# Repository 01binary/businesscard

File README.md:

# Interactive Business Card

A two-sided PCB business card designed in `KiCad 9`, built around an `ESP32-S2-MINI-2` module, powered by `USB-C` or a `CR2032` coin cell.

+ Capacitive-Touch Piano Keys (`C4`–`C5`, one octave)
+ Piezo Speaker (Monophonic Tone Playback)
+ Capacitive Logo Touch Pad (Wake / Power Control)
+ USB-C or `CR2032` Power, Auto-Switched
+ Deep Sleep for Low Power Consumption

## Modules

The following module is placed onto the board:

|Module|Function|
|-|-|
|`ESP32-S2-MINI-2-N4`|MCU module with native USB, capacitive-touch inputs, and deep sleep|

## Power

Power comes from either a `USB-C` connector (through a `3.3V` LDO regulator) or a `CR2032` coin cell battery.

A `TPS2121` power multiplexer (`U_PWR`) automatically prioritizes `USB` power when plugged in, and switches back to coin cell power when unplugged, with no interruption to the `3.3V` rail.

| Stage | Component | Function |
|-|-|-|
| `USB` → `3.3V` | `AP2112K-3.3` (`U2`) | LDO regulator, converts `VBUS` (`5V`) down to `3.3V` |
| `USB` / Battery Switch | `TPS2121` (`U_PWR`) | Selects `USB 3.3V` or `CR2032 3V`, prioritizing `USB` |
| Coin Cell | Keystone `3034` (`BT1`) | Holder for `20mm CR2032` battery |

Decoupling/bulk capacitors on the `3.3V` rail:

|Capacitor|Value|Purpose|
|-|-|-|
|`C1`|`100µF`|Bulk capacitor, stabilizes rail against low-frequency dips (battery power draw)|
|`C2`|`10µF`|LDO output filter|
|`C3`|`0.1µF`|Local high-frequency bypass near the MCU|

### USB-C Configuration

The `USB-C` receptacle (`J1`) is configured for `UFP` (Upstream Facing Port) mode, meaning the card acts as a `USB` device, not a host.

+ `CC1` and `CC2` are each pulled to `GND` through `5.1kΩ` resistors (`R1`, `R2`), advertising the device role per the `USB Type-C` spec.
+ Only one of `CC1`/`CC2` is active depending on cable orientation, but both are populated so the connector works either way.
+ When plugged in, the host detects the pull-downs and supplies `5V` on `VBUS`.
+ No `USB-PD` negotiation is needed since the board only draws default `5V` at low current.

## Touch Interface

The front of the card has 13 capacitive touch pads forming one octave of piano-style keys (`C4`–`C5`), plus a two-piece logo pad that is electrically bridged into a single touch input.

+ Touching a piano key plays its corresponding tone through the piezo speaker.
+ Touching the logo pad wakes the device from deep sleep and acts as the soft power button.
+ After a period of inactivity, the firmware drops to a reduced CPU frequency and then enters deep sleep; touching the logo is the wake source.
+ All touch pads and I/O are additionally brought out as test points for flexibility in layout and debugging.

## Audio

When a key is touched, the firmware plays a monophonic tone through a piezo transducer (`LS1`), driven differentially from two `GPIO` pins through `100Ω` series resistors (`R3`, `R4`).

## Buttons

|Button|Function|
|-|-|
|`SW1`|`RESET` — pulls `EN` low to reset the MCU|
|`SW2`|`BOOT` — pulls `GPIO0` low to enter flashing mode|

## Pins

|Pin|Function|
|-|-|
|`GPIO19`|USB `D-` (`J1`)|
|`GPIO20`|USB `D+` (`J1`)|
|`GPIO0`|`BOOT` Button (`SW2`)|
|`EN`|`RESET` Button (`SW1`)|
|`3V3`|Power input from `U_PWR` (`TPS2121`) `OUT`|
|`GPIO26`|Piezo Driver `A` → `R3` → `LS1 +`|
|`GPIO17`|Piezo Driver `B` → `R4` → `LS1 -`|
|`GPIO1`|Touch Key `C` (`TP1`)|
|`GPIO2`|Touch Key `C#` (`TP2`)|
|`GPIO3`|Touch Key `D` (`TP3`)|
|`GPIO4`|Touch Key `D#` (`TP4`)|
|`GPIO5`|Touch Key `E` (`TP5`)|
|`GPIO6`|Touch Key `F` (`TP6`)|
|`GPIO7`|Touch Key `F#` (`TP7`)|
|`GPIO8`|Touch Key `G` (`TP8`)|
|`GPIO9`|Touch Key `G#` (`TP9`)|
|`GPIO10`|Touch Key `A` (`TP10`)|
|`GPIO11`|Touch Key `A#` (`TP11`)|
|`GPIO12`|Touch Key `B` (`TP12`)|
|`GPIO13`|Touch Key `C` (octave up) (`TP13`)|
|`GPIO14`|Touch Logo Pad, wake source (`TP14`, bridged)|

## Bill of Materials

|Component|Description|
|-|-|
|[ESP32-S2-MINI-2-N4](https://www.digikey.com/en/products/result?keywords=ESP32-S2-MINI-2-N4)|Main MCU with native USB and capacitive-touch capability|
|[AP2112K-3.3TRG1DICT-ND](https://www.digikey.com/en/products/result?keywords=AP2112K-3.3TRG1)|`3.3V` LDO regulator for USB power source|
|[TPS2121RUXR](https://www.digikey.com/en/products/result?keywords=TPS2121RUXR)|Power multiplexer, auto-switches between USB `3.3V` and `CR2032` battery|
|[Keystone 3034](https://www.digikey.com/en/products/result?keywords=3034)|Holder for `20mm CR2032` battery|
|[UJ20-C-H-G-MSMT-5-P16-TR](https://www.digikey.com/en/products/result?keywords=UJ20-C-H-G-MSMT-5-P16-TR)|USB-C receptacle for power and programming|
|[TLSMDT3C020GLFS](https://www.digikey.com/en/products/detail/c-k/TLSMDT3C020GLFS/14553425)|`SW1`/`SW2` Momentary pushbutton, RESET (`EN`) and BOOT (`GPIO0`)|
|[SMT-1141-T-5-R](https://www.digikey.com/en/products/detail/pui-audio-inc/SMT-1141-T-5-R/6192576)|Piezo transducer, audio output for tone playback|
|[RMCF0603FT5K10CTND](https://www.digikey.com/en/products/result?keywords=RMCF0603FT5K10)|`5.1kΩ` `0603` resistor, USB-C `CC` pull-downs (`R1`, `R2`)|
|[RMCF0603JT100RCTND](https://www.digikey.com/en/products/result?keywords=RMCF0603JT100R)|`100Ω` `0603` resistor, piezo driver series protection (`R3`, `R4`)|
|[CL32A107MPVNNNE](https://www.digikey.com/en/products/result?keywords=CL32A107MPVNNNE)|`100µF` capacitor, bulk power stabilization (`C1`)|
|[GRM21BR61C106KE15K](https://www.digikey.com/en/products/result?keywords=GRM21BR61C106KE15K)|`10µF` `0805` capacitor, LDO output filter (`C2`)|
|[CS0805KKX7R0BB104](https://www.digikey.com/en/products/result?keywords=CS0805KKX7R0BB104)|`0.1µF` `0603` capacitor, local bypass near MCU (`C3`)|

`TP1`–`TP13` are capacitive piano key electrodes (`C4`–`C5`); `TP14` is the two-piece logo pad bridged into a single wake-source input. Neither requires a physical component.

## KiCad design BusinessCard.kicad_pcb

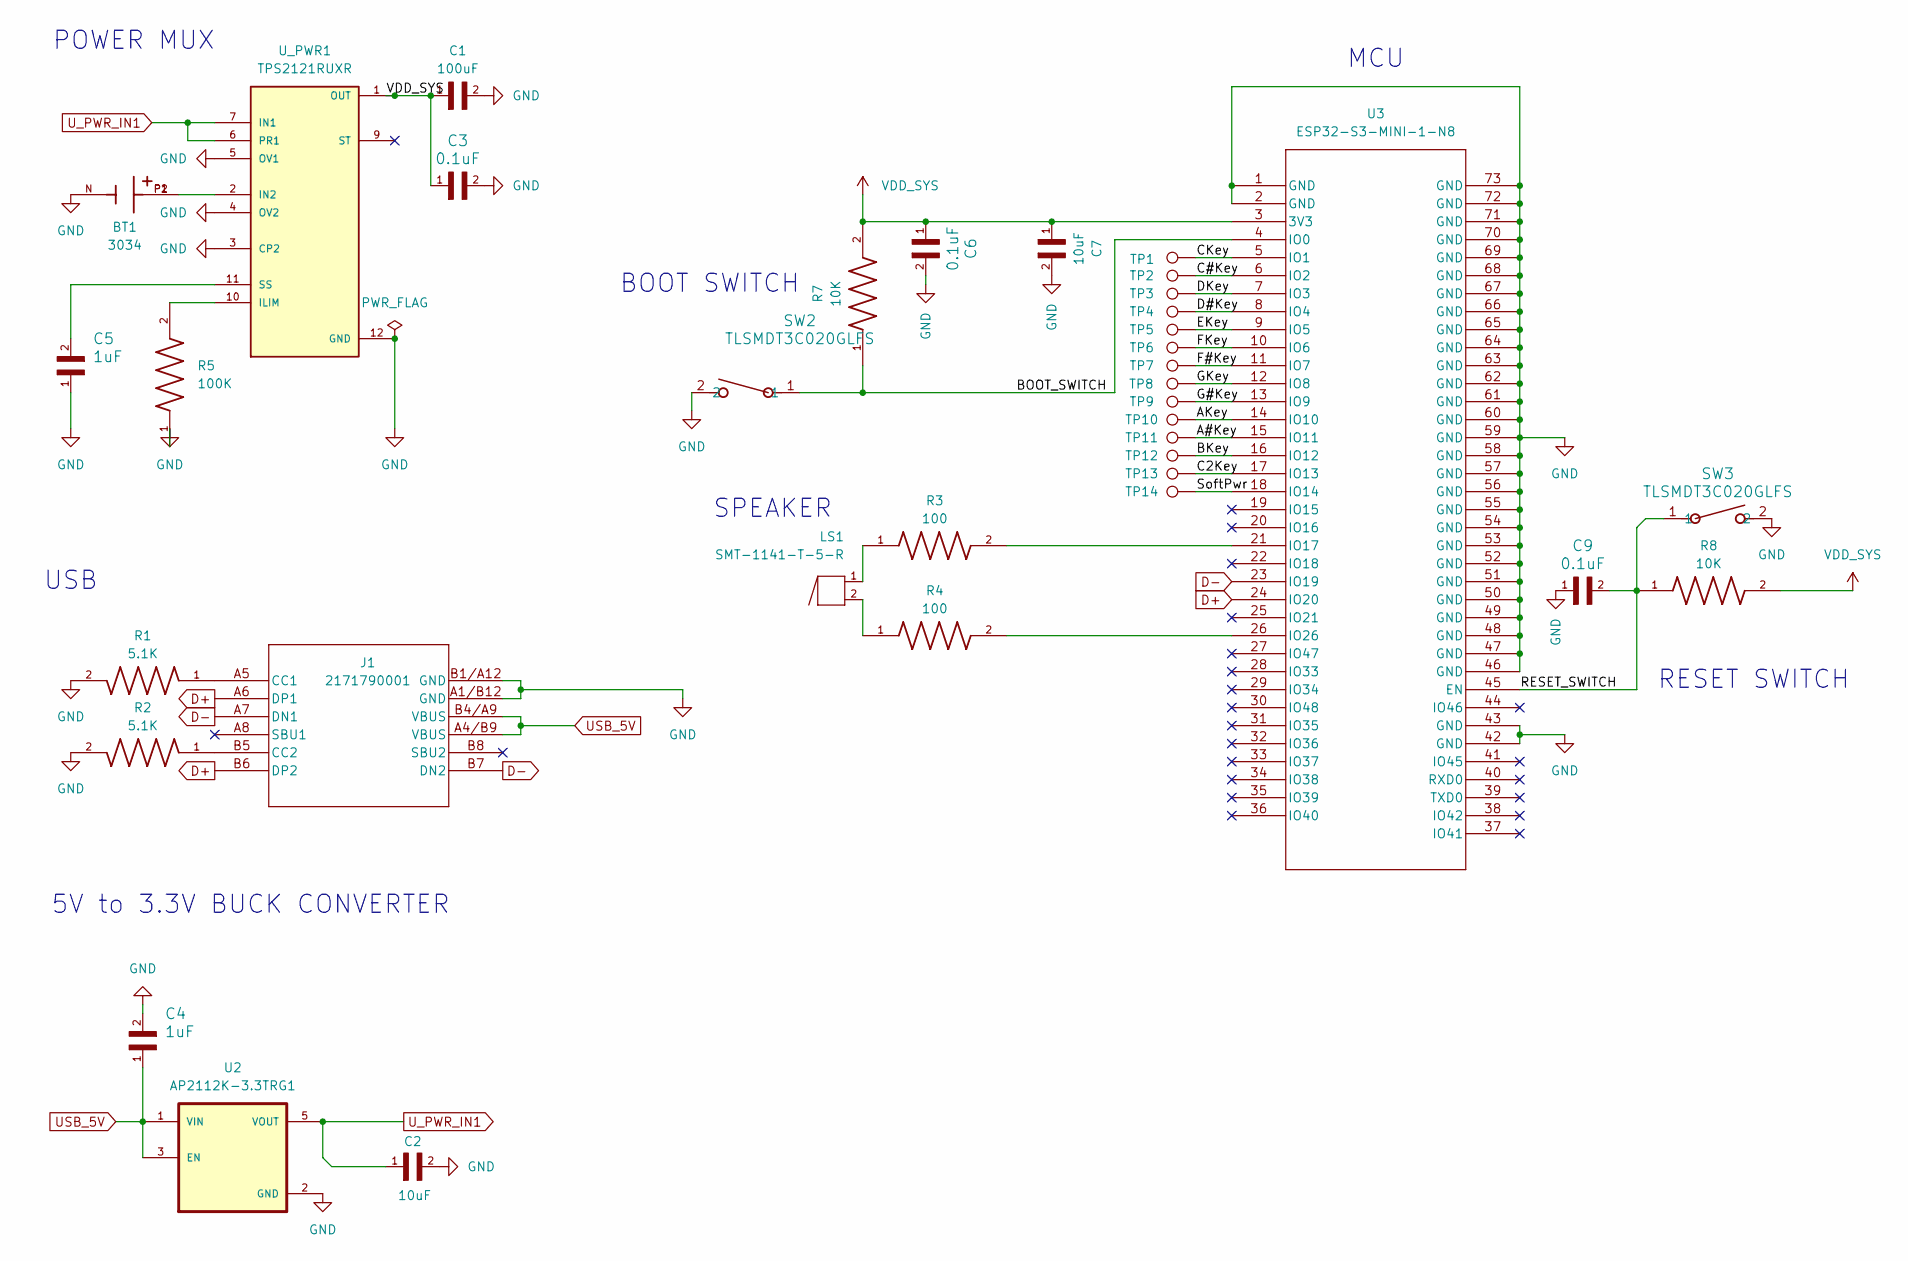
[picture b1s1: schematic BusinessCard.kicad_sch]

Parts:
BT1: 3034; BAT_3034; PARTREV E; DigiKey_Part_Number 36-3034-ND
C1: 100uF; CAPC3225X280N; LCSC C23742
C2: 10uF; CL10A106KP8NNNC; LCSC C19702
C3, C6, C9: 0.1uF; CL10B104KA8NNNC; DigiKey_Part_Number 1276-1006-1-ND
C4, C5: 1uF; GRM188R71A105KA61D; LCSC C97888
C7: 10uF; CL10A106KP8NNNC; DigiKey_Part_Number 1276-CL21A106KAYNNNFTR-ND
J1: 2171790001; 2171790001_MOL; PARTREV 1.0; LCSC C45082768
LS1: SMT-1141-T-5-R; XDCR_SMT-1141-T-5-R; PARTREV A; LCSC C6680782
R1, R2: 5.1K; RC0603FR-075K1L; LCSC C105580
R3, R4: 100; RESC1508X55N; LCSC C305084
R5: 100K; RC0805FR-07100KL; DigiKey_Part_Number 311-100KCRCT-ND
R7, R8: 10K; AF0805FR-0710KL; DigiKey_Part_Number 13-AF0805FR-0710KLCT-ND
SW2, SW3: TLSMDT3C020GLFS; TS-1088-AR02016; LCSC C720477
TP1, TP2, TP3, TP4, TP5, TP6, TP7, TP8, TP9, TP10, TP11, TP12, TP13: TestPoint; BusinessCardPad
TP14: TestPoint; BusinessCardLogo
U2: AP2112K-3.3TRG1; SOT95P285X140-5N; PARTREV 2-2; LCSC C51118
U3: ESP32-S3-MINI-1-N8; PARTREV v0.5; LCSC C2913206
U_PWR1: TPS2121RUXR; IC_TPS2121RUXR; LCSC C485916

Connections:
/A#Key: TP11.1, U3.15 (IO11)
/AKey: TP10.1, U3.14 (IO10)
/BKey: TP12.1, U3.16 (IO12)
/BOOT_SWITCH: R7.1, SW2.1, U3.4 (IO0)
/C2Key: TP13.1, U3.17 (IO13)
/C#Key: TP2.1, U3.6 (IO2)
/CKey: TP1.1, U3.5 (IO1)
/D#Key: TP4.1, U3.8 (IO4)
/DKey: TP3.1, U3.7 (IO3)
/EKey: TP5.1, U3.9 (IO5)
/F#Key: TP7.1, U3.11 (IO7)
/FKey: TP6.1, U3.10 (IO6)
/G#Key: TP9.1, U3.13 (IO9)
/GKey: TP8.1, U3.12 (IO8)
/RESET_SWITCH: C9.2, R8.1, SW3.1, U3.45 (EN)
/SoftPwr: TP14.1, U3.18 (IO14)
D+: J1.A6 (DP1), J1.B6 (DP2), U3.24 (IO20)
D-: J1.A7 (DN1), J1.B7 (DN2), U3.23 (IO19)
GND: BT1.N, C1.2, C2.2, C3.2, C4.2, C5.1, C6.2, C7.2, C9.1, J1.A1/B12 (GND), J1.B1/A12 (GND), R1.2, R2.2, R5.1, SW2.2, SW3.2, U2.2 (GND), U3.1 (GND), U3.2 (GND), U3.42 (GND), U3.43 (GND), U3.46 (GND), U3.47 (GND), U3.48 (GND), U3.49 (GND), U3.50 (GND), U3.51 (GND), U3.52 (GND), U3.53 (GND), U3.54 (GND), U3.55 (GND), U3.56 (GND), U3.57 (GND), U3.58 (GND), U3.59 (GND), U3.60 (GND), U3.61 (GND), U3.62 (GND), U3.63 (GND), U3.64 (GND), U3.65 (GND), U3.66 (GND), U3.67 (GND), U3.68 (GND), U3.69 (GND), U3.70 (GND), U3.71 (GND), U3.72 (GND), U3.73 (GND), U_PWR1.3 (CP2), U_PWR1.4 (OV2), U_PWR1.5 (OV1), U_PWR1.12 (GND)
unnamed: J1.A5 (CC1), R1.1
unnamed: J1.B5 (CC2), R2.1
unnamed: LS1.1, R3.1
unnamed: LS1.2, R4.1
unnamed: R3.2, U3.21 (IO17)
unnamed: R4.2, U3.26 (IO26)
unnamed: R5.2, U_PWR1.10 (ILIM)
unnamed: BT1.P1, BT1.P2, U_PWR1.2 (IN2)
unnamed: C5.2, U_PWR1.11 (SS)
USB_5V: C4.1, J1.A4/B9 (VBUS), J1.B4/A9 (VBUS), U2.1 (VIN), U2.3 (EN)
U_PWR_IN1: C2.1, U2.5 (VOUT), U_PWR1.6 (PR1), U_PWR1.7 (IN1)
VDD_SYS: C1.1, C3.1, C6.1, C7.1, R7.2, R8.2, U3.3 (3V3), U_PWR1.1 (OUT)

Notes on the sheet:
MCU
USB
POWER MUX
SPEAKER
RESET SWITCH
5V to 3.3V BUCK CONVERTER
BOOT SWITCH

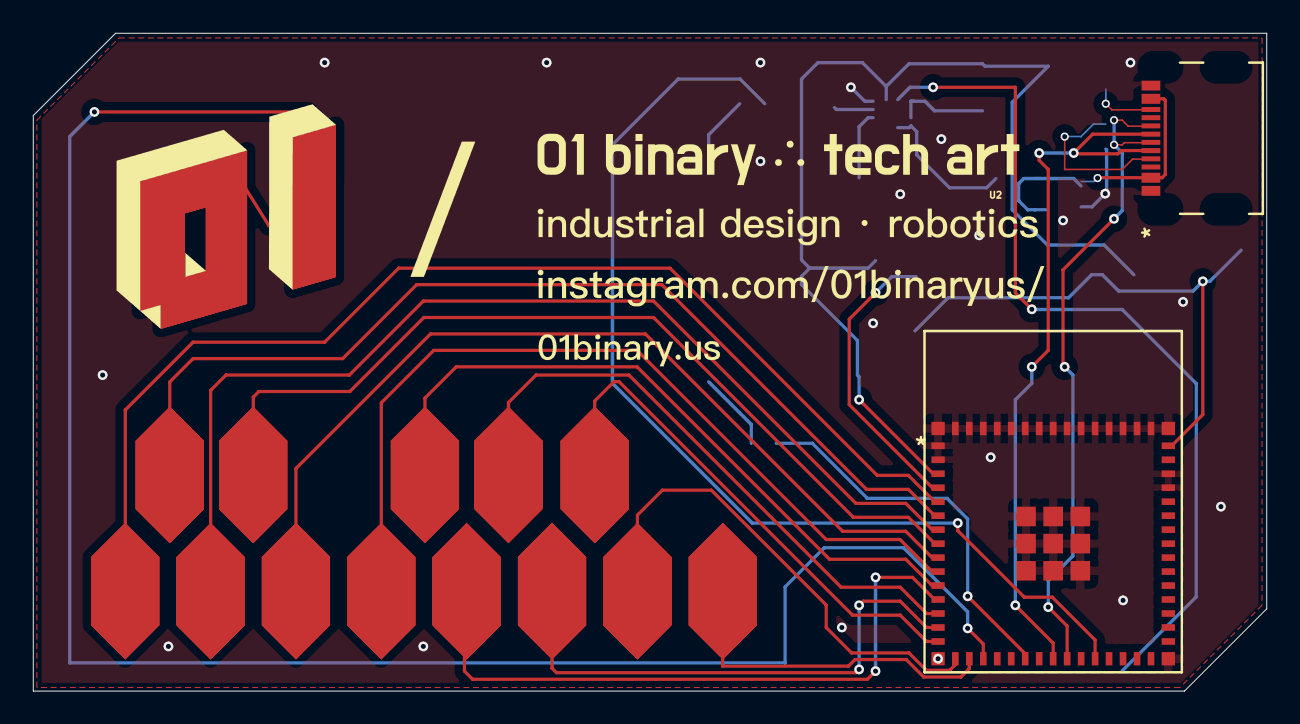
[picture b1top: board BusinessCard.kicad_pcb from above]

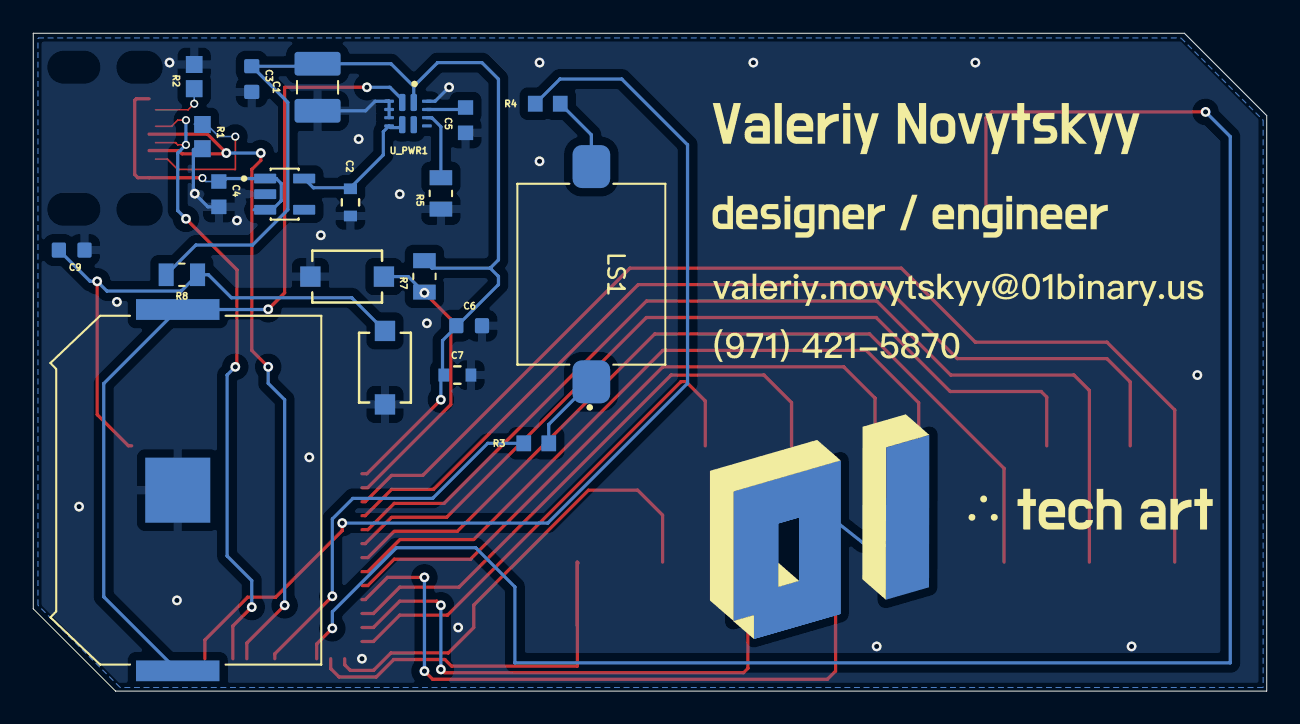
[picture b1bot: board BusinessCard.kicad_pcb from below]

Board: 2 copper layers, 75.0 x 40.0 mm, 37 parts (21 on the bottom side), 31 nets.

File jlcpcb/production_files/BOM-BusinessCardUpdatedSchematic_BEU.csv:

Comment,Designator,Footprint,LCSC,Quantity
0.1uF,"C3,C6,C9",CL10B104KA8NNNC,C1590,3
100,"R3,R4",RESC1508X55N,C305084,2
100K,R5,RC0805FR-07100KL,C96346,1
100uF,C1,CAPC3225X280N,C23742,1
10K,"R7,R8",AF0805FR-0710KL,C192906,2
10uF,"C2,C7",CL10A106KP8NNNC,C19702,2
1uF,"C4,C5",GRM188R71A105KA61D,C97888,2
2171790001,J1,2171790001_MOL,C45082768,1
3034,BT1,BAT_3034,C5213768,1
5.1K,"R1,R2",RC0603FR-075K1L,C105580,2
AP2112K-3.3TRG1,U2,SOT95P285X140-5N,C51118,1
ESP32-S3-MINI-1-N8,U3,ESP32-S3-MINI-1-N8,C2913206,1
TLSMDT3C020GLFS,"SW2,SW3",TS-1088-AR02016,C720477,2
TPS2121RUXR,U_PWR1,IC_TPS2121RUXR,C485916,1
